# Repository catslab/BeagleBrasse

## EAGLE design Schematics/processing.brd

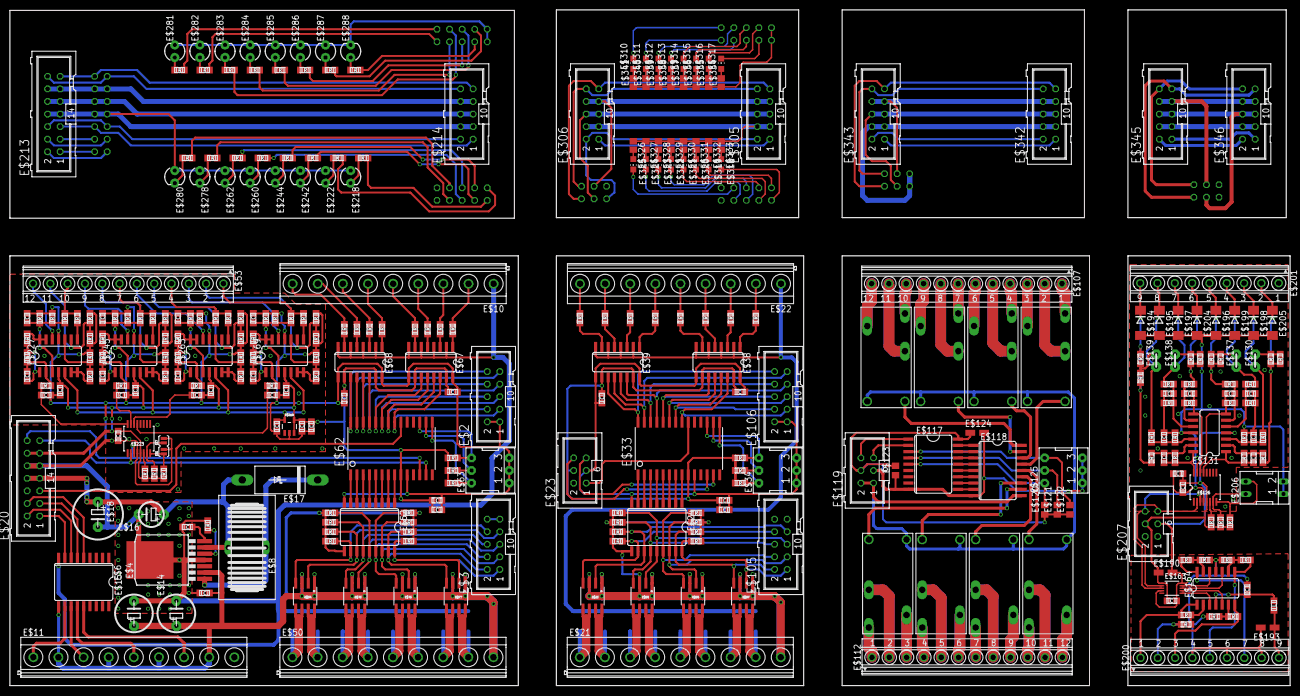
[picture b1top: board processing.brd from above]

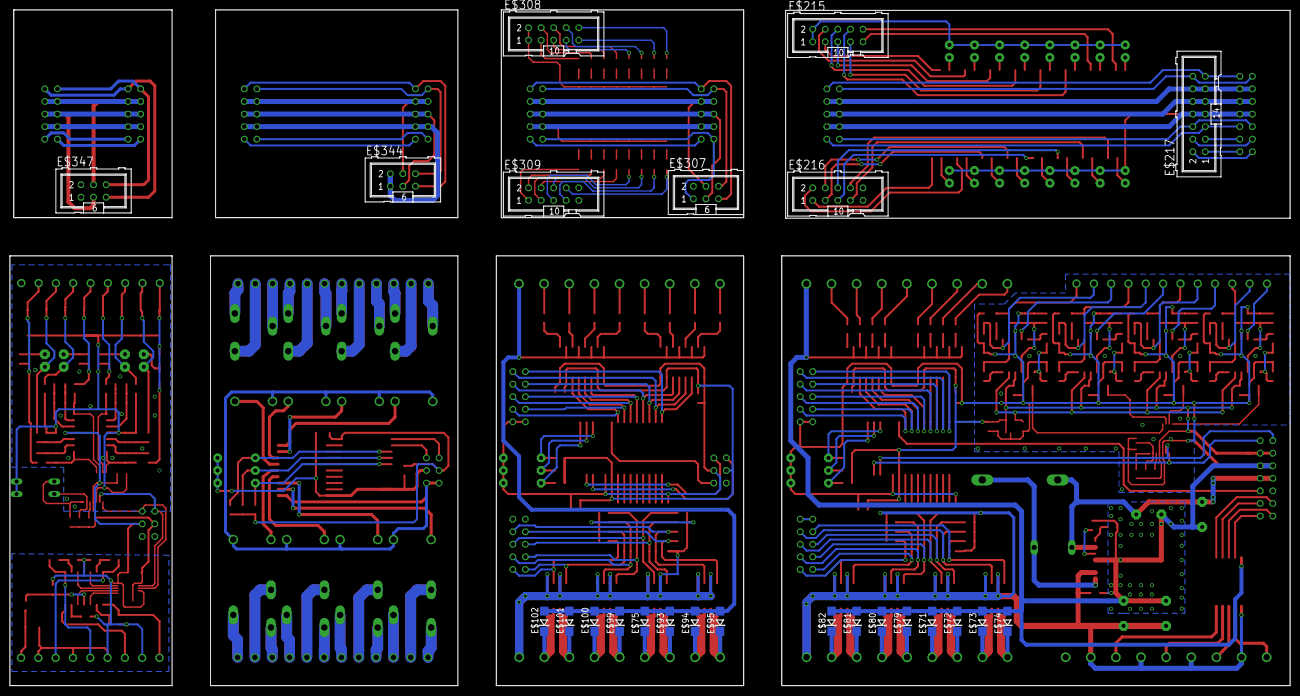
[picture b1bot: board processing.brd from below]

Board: 2 copper layers, 258.9 x 136.6 mm, 347 parts (24 on the bottom side), 366 nets.

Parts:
E$1, E$7: SJ_2S-NO
E$2, E$3, E$105, E$106, E$214, E$215, E$216, E$305, E$306, E$308, E$309, E$342, E$343, E$345, E$346: ML10
E$4: LM2673; DDPACK-7
E$5, E$9, E$13, E$48, E$69, E$83, E$84, E$103, E$104, E$134, E$144, E$146, E$150, E$152, E$156, E$158, E$162, E$191, E$192, E$202: 100n; C0805
E$6, E$24, E$52, E$118: ULN2803; SO18L
E$8: KM3.0
E$10, E$11, E$21, E$22, E$50: MKDSN1,5/9-5,08
E$12, E$19, E$26, E$27, E$28, E$29, E$30, E$31, E$32, E$35, E$36, E$37, E$49, E$55, E$56, E$57, E$58, E$59, E$60, E$61, E$64, E$65, E$66, E$120, E$121, E$122, E$127, E$128, E$129, E$224, E$225, E$226: 10K; R0805
E$14, E$15: CE02D
E$16: CE02C
E$17: DO201T15
E$18: CE02A
E$20, E$213, E$217: ML14
E$23, E$119, E$207, E$307, E$344, E$347: ML6
E$25, E$54, E$76, E$77, E$78, E$96, E$97, E$98: SOIC8
E$33, E$62: MCP23017; SO28-3
E$34, E$63, E$125: EPG-03-SMALL
E$38, E$39, E$67, E$68: ACSL-6400; SO16
E$40, E$41, E$42, E$43, E$44, E$45, E$46, E$47, E$85, E$86, E$87, E$88, E$89, E$90, E$91, E$92: 1.30K; R0805
E$51, E$70, E$203: 1u; C0805
E$53, E$107, E$112: 175317
E$71, E$72, E$73, E$74, E$75, E$79, E$80, E$81, E$82, E$93, E$94, E$95, E$99, E$100, E$101, E$102: DO214AC
E$108, E$109, E$110, E$111, E$113, E$114, E$115, E$116: ALQ105; ALQ
E$117: MCP2308; SO18W
E$123: 100n; R0805
E$124, E$190, E$193: 10u; CT3216
E$126: ADC128D818; TSSOP16
E$130, E$137, E$138, E$139: J01N
E$131: LMV344; SOIC-14
E$132, E$143, E$145, E$149, E$151, E$155, E$157, E$161: 25.5K; R0805
E$133, E$140, E$141, E$142, E$209, E$210, E$211, E$212: 500; R0805
E$135, E$136, E$147, E$148, E$153, E$154, E$159, E$160: 102K; R0805
E$163: MCP4728; MSOP10
E$164: OPA4171; SOIC-14
E$165, E$167, E$186, E$187: 82.5K; R0805
E$166, E$168, E$188, E$189: 330K; R0805
E$169, E$227, E$245, E$263: SOIC-14
E$170, E$175, E$184, E$185, E$220, E$221, E$228, E$233, E$243, E$246, E$251, E$261, E$264, E$269, E$279: 0.1; C0805
E$171, E$179, E$229, E$237, E$247, E$255, E$265, E$273: 1K; R0805
E$172, E$173, E$230, E$231, E$248, E$249, E$266, E$267: 2K; R0805
E$174, E$178, E$232, E$236, E$250, E$254, E$268, E$272: 39.2K; R0805
E$176, E$234, E$252, E$270: 1.91K; R0805
E$177, E$235, E$253, E$271: 100; R0805
E$180, E$238, E$256, E$274: 26.7K; R0805
E$181, E$239, E$257, E$275: 1.1K; R0805
E$182, E$240, E$258, E$276: 4.7n; C0805
E$183, E$241, E$259, E$277: 51; R0805
E$194, E$196, E$197, E$198, E$199, E$204, E$205: 1SMB30AT3G; DO214AA
E$195: DO214AA
E$200, E$201: 1751316
E$206: EPG-02
E$208: 10uH; L0805
E$218, E$222, E$242, E$244, E$260, E$262, E$278, E$280, E$281, E$282, E$283, E$284, E$285, E$286, E$287, E$288: LED3MM
E$219: SOT23-5
E$223: AD5316R; TSSOP16
E$289, E$290, E$291, E$292, E$293, E$294, E$295, E$296, E$297, E$298, E$299, E$300, E$301, E$302, E$303, E$304: 470; R0805
E$310, E$311, E$312, E$313, E$314, E$315, E$316, E$317, E$318, E$319, E$320, E$321, E$322, E$323, E$324, E$325: CHIP-LED0805
E$326, E$327, E$328, E$329, E$330, E$331, E$332, E$333, E$334, E$335, E$336, E$337, E$338, E$339, E$340, E$341: R0805

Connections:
3V1: E$117.18, E$119.4, E$120.1, E$121.1, E$122.1, E$123.2, E$124.+
3V2: E$342.7, E$342.8, E$343.7, E$343.8, E$344.4
3V3: E$23.4, E$33.9, E$35.1, E$36.1, E$37.1, E$38.10, E$38.15, E$39.10, E$39.15, E$48.1, E$51.1, E$103.2, E$104.2
3V4: E$345.7, E$345.8, E$346.7, E$346.8, E$347.4
5V: E$108.P$1, E$109.P$1, E$110.P$1, E$111.P$1, E$113.P$1, E$114.P$1, E$115.P$1, E$116.P$1, E$118.10, E$119.1, E$119.2
5V1: E$345.3, E$345.4, E$346.3, E$346.4
+5V: E$4.6, E$8.2, E$16.+, E$17.A, E$18.+, E$20.7, E$20.8
GND: E$1.2, E$2.1, E$2.2, E$4.4, E$4.P$1, E$5.1, E$6.9, E$7.2, E$9.2, E$10.1, E$12.2, E$13.1, E$14.-, E$15.-, E$16.-, E$18.-, E$20.9, E$20.10, E$52.9, E$62.10, E$63.1, E$63.2, E$63.3, E$67.2, E$67.4, E$67.6, E$67.8, E$67.9, E$67.16, E$68.2, E$68.4, E$68.6, E$68.8, E$68.9, E$68.16, E$69.2, E$70.2, E$71.A, E$72.A, E$73.A, E$74.A, E$79.A, E$80.A, E$81.A, E$82.A, E$83.1, E$84.1, E$169.11, E$173.1, E$174.1, E$175.2, E$176.1, E$177.2, E$181.2, E$182.1, E$184.1, E$185.2, E$219.2, E$220.1, E$221.1, E$223.4, E$227.11, E$231.1, E$232.1, E$233.2, E$234.1, E$235.2, E$239.2, E$240.1, E$243.2, E$245.11, E$249.1, E$250.1, E$251.2, E$252.1, E$253.2, E$257.2, E$258.1, E$261.2, E$263.11, E$267.1, E$268.1, E$269.2, E$270.1, E$271.2, E$275.2, E$276.1, E$279.2
GND1: E$23.3, E$24.9, E$33.10, E$34.1, E$34.2, E$34.3, E$38.9, E$38.16, E$39.9, E$39.16, E$48.2, E$51.2, E$103.1, E$104.1, E$106.1, E$106.2
GND2: E$117.9, E$118.9, E$119.3, E$123.1, E$124.-, E$125.1, E$125.2, E$125.3
GND3: E$126.4, E$126.5, E$127.2, E$128.2, E$129.2, E$131.4, E$131.11, E$143.1, E$144.1, E$145.2, E$146.2, E$155.1, E$156.1, E$157.2, E$158.2, E$163.1, E$163.4, E$163.10, E$164.11, E$165.2, E$167.2, E$186.1, E$187.1, E$190.+, E$190.-, E$191.1, E$191.2, E$192.1, E$193.-, E$194.A, E$195.A, E$196.A, E$197.A, E$198.A, E$199.A, E$200.2, E$200.4, E$200.6, E$200.8, E$202.1, E$202.2, E$203.1, E$203.2, E$204.A, E$205.A, E$206.1, E$206.2, E$207.3, E$207.4
GND4: E$342.5, E$342.6, E$343.5, E$343.6, E$344.3
GND5: E$345.5, E$345.6, E$346.5, E$346.6, E$347.3
IN1+: E$139.1, E$160.2, E$195.C, E$201.8
IN1-: E$142.2, E$159.2, E$194.C, E$201.9, E$212.2
IN2+: E$138.1, E$153.2, E$197.C, E$201.7
IN2-: E$141.2, E$154.2, E$201.6, E$204.C, E$211.2
IN3+: E$137.1, E$148.2, E$199.C, E$201.4
IN3-: E$140.2, E$147.2, E$196.C, E$201.5, E$210.2
IN4+: E$130.1, E$135.2, E$198.C, E$201.3
IN4-: E$133.2, E$136.2, E$201.2, E$205.C, E$209.2
INT1: E$23.1, E$33.20
POWER_GND: E$22.1, E$38.2, E$38.4, E$38.6, E$38.8, E$39.2, E$39.4, E$39.6, E$39.8, E$75.A, E$93.A, E$94.A, E$95.A, E$99.A, E$100.A, E$101.A, E$102.A
S$8: E$10.9, E$85.2
S$11: E$53.1, E$171.1, E$172.1
S$26: E$6.11, E$11.1
S$27: E$6.12, E$11.3
S$28: E$6.13, E$11.5
S$29: E$6.14, E$11.7
S$34: E$1.1, E$223.8, E$224.1
S$35: E$6.6, E$20.3
S$36: E$6.5, E$20.4
S$37: E$6.7, E$20.2
S$38: E$6.8, E$20.1
S$39: E$10.8, E$86.2
S$40: E$10.7, E$87.2
S$41: E$10.6, E$88.2
S$42: E$10.5, E$89.2
S$43: E$10.4, E$90.2
S$44: E$10.3, E$91.2
S$45: E$10.2, E$92.2
S$46: E$68.7, E$85.1
S$81: E$4.2, E$6.10, E$11.2, E$11.4, E$11.6, E$11.8, E$13.2, E$14.+, E$15.+, E$49.1, E$50.9, E$52.10, E$54.1, E$54.3, E$55.1, E$56.1, E$57.1, E$58.2, E$59.2, E$60.2, E$61.2, E$76.1, E$76.3, E$77.1, E$77.3, E$78.1, E$78.3
S$82: E$4.1, E$8.1, E$17.C
S$83: E$4.7, E$5.2
S$85: E$4.5, E$12.1
S$99: E$169.8, E$171.2
S$102: E$169.6, E$169.7, E$180.2
S$105: E$53.2, E$169.9, E$176.2, E$177.1
S$108: E$169.1, E$170.1, E$178.1, E$179.1
S$114: E$169.2, E$170.2, E$178.2, E$183.1
S$120: E$169.13, E$169.14, E$179.2
S$126: E$169.10, E$180.1, E$181.1
S$132: E$169.3, E$172.2, E$173.2, E$174.2, E$175.1
S$133: E$53.3, E$169.12
S$134: E$182.2, E$183.2, E$223.13
S$145: E$3.9, E$3.10
S$151: E$169.5, E$184.2, E$219.5, E$227.5, E$245.5, E$263.5
S$152: E$3.8, E$49.2, E$52.11, E$54.4
S$153: E$3.7, E$52.12, E$54.2, E$55.2
S$155: E$19.2, E$24.11, E$25.4, E$105.8
S$156: E$24.12, E$25.2, E$26.2, E$105.7
S$157: E$24.13, E$27.2, E$98.4, E$105.6
S$158: E$3.6, E$52.13, E$56.2, E$78.4
S$159: E$3.5, E$52.14, E$57.2, E$78.2
S$160: E$3.4, E$52.15, E$58.1, E$76.4
S$162: E$3.3, E$52.16, E$59.1, E$76.2
S$163: E$3.2, E$52.17, E$60.1, E$77.4
S$164: E$3.1, E$52.18, E$61.1, E$77.2
S$165: E$24.14, E$28.2, E$98.2, E$105.5
S$166: E$52.8, E$62.1
S$167: E$52.7, E$62.2
S$168: E$52.6, E$62.3
S$169: E$52.5, E$62.4
S$170: E$52.4, E$62.5
S$171: E$52.3, E$62.6
S$172: E$52.2, E$62.7
S$173: E$52.1, E$62.8
S$174: E$24.15, E$29.1, E$96.4, E$105.4
S$178: E$24.16, E$30.1, E$96.2, E$105.3
S$180: E$24.17, E$31.1, E$97.4, E$105.2
S$182: E$2.10, E$62.28, E$68.11
S$183: E$2.9, E$62.27, E$68.12
S$184: E$2.8, E$62.26, E$68.13
S$185: E$2.7, E$62.25, E$68.14
S$186: E$2.6, E$62.24, E$67.11
S$187: E$2.5, E$62.23, E$67.12
S$188: E$2.4, E$62.22, E$67.13
S$189: E$2.3, E$62.21, E$67.14
S$190: E$20.5, E$62.20
S$191: E$62.17, E$63.4, E$65.2
S$192: E$62.16, E$63.5, E$64.2
S$193: E$62.15, E$63.6, E$66.2
S$194: E$50.1, E$54.5, E$54.6, E$74.C
S$195: E$53.19, E$229.1, E$230.1
S$196: E$227.8, E$229.2
S$197: E$227.6, E$227.7, E$238.2
S$198: E$53.20, E$227.9, E$234.2, E$235.1
S$199: E$227.1, E$228.1, E$236.1, E$237.1
S$200: E$227.2, E$228.2, E$236.2, E$241.1
S$201: E$227.13, E$227.14, E$237.2
S$202: E$227.10, E$238.1, E$239.1
S$203: E$50.2, E$54.7, E$54.8, E$73.C
S$204: E$227.3, E$230.2, E$231.2, E$232.2, E$233.1
S$205: E$53.21, E$227.12
S$206: E$223.16, E$240.2, E$241.2
S$207: E$50.5, E$76.5, E$76.6, E$79.C
S$208: E$50.6, E$76.7, E$76.8, E$80.C
S$209: E$53.7, E$247.1, E$248.1
S$210: E$245.8, E$247.2
S$211: E$245.6, E$245.7, E$256.2
S$212: E$53.8, E$245.9, E$252.2, E$253.1
S$213: E$245.1, E$246.1, E$254.1, E$255.1
S$214: E$245.2, E$246.2, E$254.2, E$259.1
S$215: E$245.13, E$245.14, E$255.2
S$216: E$245.10, E$256.1, E$257.1
S$217: E$50.7, E$77.5, E$77.6, E$81.C
S$218: E$245.3, E$248.2, E$249.2, E$250.2, E$251.1
S$219: E$53.9, E$245.12
S$220: E$223.15, E$258.2, E$259.2
S$221: E$50.8, E$77.7, E$77.8, E$82.C
S$222: E$50.3, E$72.C, E$78.5, E$78.6
S$223: E$53.4, E$265.1, E$266.1
S$224: E$263.8, E$265.2
S$225: E$263.6, E$263.7, E$274.2
S$226: E$53.5, E$263.9, E$270.2, E$271.1
S$227: E$263.1, E$264.1, E$272.1, E$273.1
S$228: E$263.2, E$264.2, E$272.2, E$277.1
S$229: E$263.13, E$263.14, E$273.2
S$230: E$263.10, E$274.1, E$275.1
S$231: E$223.6, E$226.1
S$232: E$263.3, E$266.2, E$267.2, E$268.2, E$269.1
S$233: E$53.6, E$263.12
S$234: E$223.14, E$276.2, E$277.2
S$235: E$7.1, E$223.7, E$225.1
S$236: E$50.4, E$71.C, E$78.7, E$78.8
S$237: E$24.18, E$32.1, E$97.2, E$105.1
S$238: E$19.1, E$21.9, E$24.10, E$25.1, E$25.3, E$26.1, E$27.1, E$28.1, E$29.2, E$30.2, E$31.2, E$32.2, E$96.1, E$96.3, E$97.1, E$97.3, E$98.1, E$98.3
S$239: E$24.8, E$33.1
S$240: E$68.5, E$86.1
S$241: E$68.3, E$87.1
S$242: E$68.1, E$88.1
S$243: E$67.7, E$89.1
S$244: E$67.5, E$90.1
S$245: E$67.3, E$91.1
S$246: E$67.1, E$92.1
S$247: E$24.7, E$33.2
S$248: E$24.6, E$33.3
S$249: E$24.5, E$33.4
S$250: E$24.4, E$33.5
S$251: E$24.3, E$33.6
S$252: E$24.2, E$33.7
S$253: E$24.1, E$33.8
S$255: E$22.9, E$40.2
S$256: E$22.8, E$41.2
S$257: E$22.7, E$42.2
S$258: E$22.6, E$43.2
S$259: E$22.5, E$44.2
S$260: E$22.4, E$45.2
S$261: E$22.3, E$46.2
S$262: E$22.2, E$47.2
S$263: E$33.28, E$39.11, E$106.10
S$264: E$33.27, E$39.12, E$106.9
S$265: E$33.26, E$39.13, E$106.8
S$266: E$33.25, E$39.14, E$106.7
S$267: E$33.24, E$38.11, E$106.6
S$268: E$33.23, E$38.12, E$106.5
S$269: E$33.22, E$38.13, E$106.4
S$270: E$33.21, E$38.14, E$106.3
S$271: E$33.17, E$34.4, E$36.2
S$272: E$33.16, E$34.5, E$35.2
S$273: E$33.15, E$34.6, E$37.2
S$274: E$21.1, E$25.5, E$25.6, E$95.C
S$275: E$21.2, E$25.7, E$25.8, E$94.C
S$276: E$21.5, E$96.5, E$96.6, E$99.C
S$277: E$21.6, E$96.7, E$96.8, E$100.C
S$278: E$21.7, E$97.5, E$97.6, E$101.C
S$279: E$21.8, E$97.7, E$97.8, E$102.C
S$280: E$21.3, E$93.C, E$98.5, E$98.6
S$281: E$21.4, E$75.C, E$98.7, E$98.8
S$283: E$39.7, E$40.1
S$284: E$39.5, E$41.1
S$285: E$39.3, E$42.1
S$286: E$39.1, E$43.1
S$287: E$38.7, E$44.1
S$288: E$38.5, E$45.1
S$289: E$38.3, E$46.1
S$290: E$38.1, E$47.1
S$313: E$107.21, E$109.P$5
S$314: E$107.20, E$109.P$3
S$315: E$107.19, E$109.P$4
S$316: E$107.8, E$108.P$3
S$317: E$107.6, E$111.P$5
S$318: E$107.5, E$111.P$3
S$319: E$107.3, E$110.P$5
S$320: E$107.2, E$110.P$3
S$321: E$107.9, E$108.P$5
S$322: E$107.7, E$108.P$4
S$323: E$107.4, E$111.P$4
S$324: E$107.1, E$110.P$4
S$337: E$112.21, E$114.P$5
S$338: E$112.20, E$114.P$3
S$339: E$112.19, E$114.P$4
S$340: E$112.8, E$113.P$3
S$341: E$112.6, E$116.P$5
S$342: E$112.5, E$116.P$3
S$343: E$112.3, E$115.P$5
S$344: E$112.2, E$115.P$3
S$345: E$112.9, E$113.P$5
S$346: E$112.7, E$113.P$4
S$347: E$112.4, E$116.P$4
S$348: E$112.1, E$115.P$4
S$361: E$117.17, E$118.1
S$362: E$117.16, E$118.2
S$363: E$117.15, E$118.3
S$364: E$117.14, E$118.4
S$365: E$117.13, E$118.5
S$366: E$117.12, E$118.6
S$367: E$117.11, E$118.7
S$368: E$117.10, E$118.8
S$369: E$109.P$2, E$118.18
S$370: E$108.P$2, E$118.17
S$371: E$111.P$2, E$118.16
S$372: E$110.P$2, E$118.15
S$373: E$114.P$2, E$118.14
S$374: E$113.P$2, E$118.13
S$375: E$116.P$2, E$118.12
S$376: E$115.P$2, E$118.11
S$377: E$117.3, E$122.2, E$125.4
S$378: E$117.4, E$121.2, E$125.5
S$379: E$117.5, E$120.2, E$125.6
S$402: E$126.6, E$129.1
S$403: E$126.7, E$128.1, E$206.4
S$404: E$126.8, E$127.1, E$206.3
S$405: E$130.2, E$133.1, E$209.1
S$406: E$131.2, E$132.1, E$134.1, E$136.1
S$407: E$131.6, E$147.1, E$149.2, E$150.2
S$408: E$126.13, E$131.1, E$132.2, E$134.2
S$409: E$131.5, E$145.1, E$146.1, E$148.1
S$410: E$138.2, E$141.1, E$211.1
S$411: E$137.2, E$140.1, E$210.1
S$412: E$131.3, E$135.1, E$143.2, E$144.2
S$413: E$126.14, E$131.7, E$149.1, E$150.1
S$414: E$131.9, E$151.1, E$152.1, E$154.1
S$415: E$131.13, E$159.1, E$161.2, E$162.2
S$416: E$126.15, E$131.8, E$151.2, E$152.2
S$417: E$131.12, E$157.1, E$158.1, E$160.1
S$418: E$131.10, E$153.1, E$155.2, E$156.2
S$419: E$126.16, E$131.14, E$161.1, E$162.1
S$420: E$163.6, E$164.3
S$421: E$163.7, E$164.5
S$422: E$163.9, E$164.12
S$423: E$163.8, E$164.10
S$424: E$164.2, E$165.1, E$166.2
S$425: E$164.1, E$166.1, E$200.1
S$426: E$164.7, E$168.2, E$200.3
S$427: E$164.13, E$186.2, E$189.2
S$428: E$164.9, E$187.2, E$188.1
S$429: E$164.14, E$189.1, E$200.7
S$430: E$164.8, E$188.2, E$200.5
S$432: E$139.2, E$142.1, E$212.1
S$433: E$126.2, E$163.3, E$207.5
S$434: E$164.6, E$167.1, E$168.1
S$435: E$193.+, E$200.9, E$208.1
S$509: E$213.11, E$213.12, E$214.7, E$214.8, E$217.11, E$217.12
S$510: E$213.9, E$213.10, E$214.5, E$214.6, E$217.9, E$217.10
S$511: E$213.6, E$214.2, E$217.6
S$512: E$213.5, E$214.1, E$217.5
S$513: E$213.4, E$217.4
S$514: E$213.3, E$217.3
S$515: E$213.2, E$217.2
S$516: E$213.1, E$217.1
S$517: E$213.7, E$213.8, E$214.3, E$214.4, E$217.7, E$217.8, E$218.A, E$222.A, E$242.A, E$244.A, E$260.A, E$262.A, E$278.A, E$280.A
S$518: E$280.K, E$289.1
S$519: E$216.8, E$289.2
S$520: E$278.K, E$290.1
S$521: E$216.7, E$290.2
S$522: E$262.K, E$291.2
S$523: E$260.K, E$292.2
S$524: E$216.6, E$291.1
S$525: E$216.5, E$292.1
S$526: E$216.4, E$293.1
S$527: E$216.3, E$294.1
S$528: E$216.2, E$295.1
S$529: E$216.1, E$296.1
S$530: E$244.K, E$293.2
S$531: E$242.K, E$294.2
S$532: E$222.K, E$295.2
S$533: E$218.K, E$296.2
S$534: E$215.10, E$297.2
S$535: E$215.9, E$298.2
S$536: E$215.8, E$299.2
S$537: E$215.7, E$300.2
S$538: E$215.6, E$301.2
S$539: E$215.5, E$302.2
S$540: E$215.4, E$303.2
S$541: E$215.3, E$304.2
S$542: E$215.1, E$215.2, E$281.K, E$282.K, E$283.K, E$284.K, E$285.K, E$286.K, E$287.K, E$288.K
S$543: E$281.A, E$297.1
S$544: E$282.A, E$298.1
S$545: E$283.A, E$299.1
S$546: E$284.A, E$300.1
S$547: E$285.A, E$301.1
S$548: E$286.A, E$302.1
S$549: E$287.A, E$303.1
S$550: E$288.A, E$304.1
S$624: E$305.10, E$306.10, E$307.6
S$625: E$305.9, E$306.9, E$307.5
S$626: E$305.5, E$305.6, E$306.5, E$306.6, E$307.3
S$627: E$305.2, E$306.2, E$307.1
S$628: E$305.1, E$306.1
S$631: E$305.7, E$305.8, E$306.7, E$306.8, E$307.4
S$632: E$305.3, E$305.4, E$306.3, E$306.4, E$326.1, E$327.1, E$328.1, E$329.1, E$330.1, E$331.1, E$332.1, E$333.1
S$633: E$309.8, E$325.C
S$634: E$309.7, E$324.C
S$635: E$309.6, E$323.C
S$636: E$309.5, E$322.C
S$637: E$309.4, E$321.C
S$638: E$309.3, E$320.C
S$639: E$309.2, E$319.C
S$640: E$309.1, E$318.C
S$641: E$325.A, E$326.2
S$642: E$324.A, E$327.2
S$643: E$323.A, E$328.2
S$644: E$322.A, E$329.2
S$645: E$321.A, E$330.2
S$646: E$320.A, E$331.2
S$647: E$319.A, E$332.2
S$648: E$318.A, E$333.2
S$649: E$317.A, E$334.2
S$650: E$316.A, E$335.2
S$651: E$315.A, E$336.2
S$652: E$314.A, E$337.2
S$653: E$313.A, E$338.2
S$654: E$312.A, E$339.2
S$655: E$311.A, E$340.2
S$656: E$310.A, E$341.2
S$657: E$308.10, E$310.C
S$658: E$308.9, E$311.C
S$659: E$308.8, E$312.C
S$660: E$308.7, E$313.C
S$661: E$308.6, E$314.C
S$662: E$308.5, E$315.C
S$663: E$308.4, E$316.C
S$664: E$308.3, E$317.C
S$665: E$308.1, E$308.2, E$334.1, E$335.1, E$336.1, E$337.1, E$338.1, E$339.1, E$340.1, E$341.1
S$739: E$342.2, E$343.2
S$740: E$342.1, E$343.1
S$743: E$342.3, E$342.4, E$343.3, E$343.4, E$344.1, E$344.2
S$744: E$345.1, E$346.1
S$745: E$345.2, E$346.2
SCL: E$20.14, E$62.12, E$223.3
SCL1: E$23.6, E$33.12
SCL2: E$117.1, E$119.6
SCL3: E$126.3, E$163.2, E$207.6
SCL4: E$213.14, E$214.10, E$217.14
SCL5: E$342.10, E$343.10, E$344.6
SCL6: E$345.10, E$346.10, E$347.6
SDA: E$20.13, E$62.13, E$223.2
SDA1: E$23.5, E$33.13
SDA2: E$117.2, E$119.5
SDA3: E$213.13, E$214.9, E$217.13
SDA4: E$342.9, E$343.9, E$344.5
SDA5: E$345.9, E$346.9, E$347.5
VCC: E$9.1, E$20.11, E$20.12, E$62.9, E$64.1, E$65.1, E$66.1, E$67.10, E$67.15, E$68.10, E$68.15, E$69.1, E$70.1, E$83.2, E$84.2, E$169.4, E$185.1, E$219.3, E$219.4, E$220.2, E$221.2, E$223.5, E$224.2, E$225.2, E$226.2, E$227.4, E$243.1, E$245.4, E$261.1, E$263.4, E$279.1
VCC1: E$164.4, E$192.2, E$208.2

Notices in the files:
parts and their libraries:
SparkFun-DigitalIC: Licensing: Creative Commons ShareAlike 4.0 International - https://creativecommons.org/licenses/by-sa/4.0
